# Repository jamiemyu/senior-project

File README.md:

# Senior_Design
Senior Design: Sleep State Analysis

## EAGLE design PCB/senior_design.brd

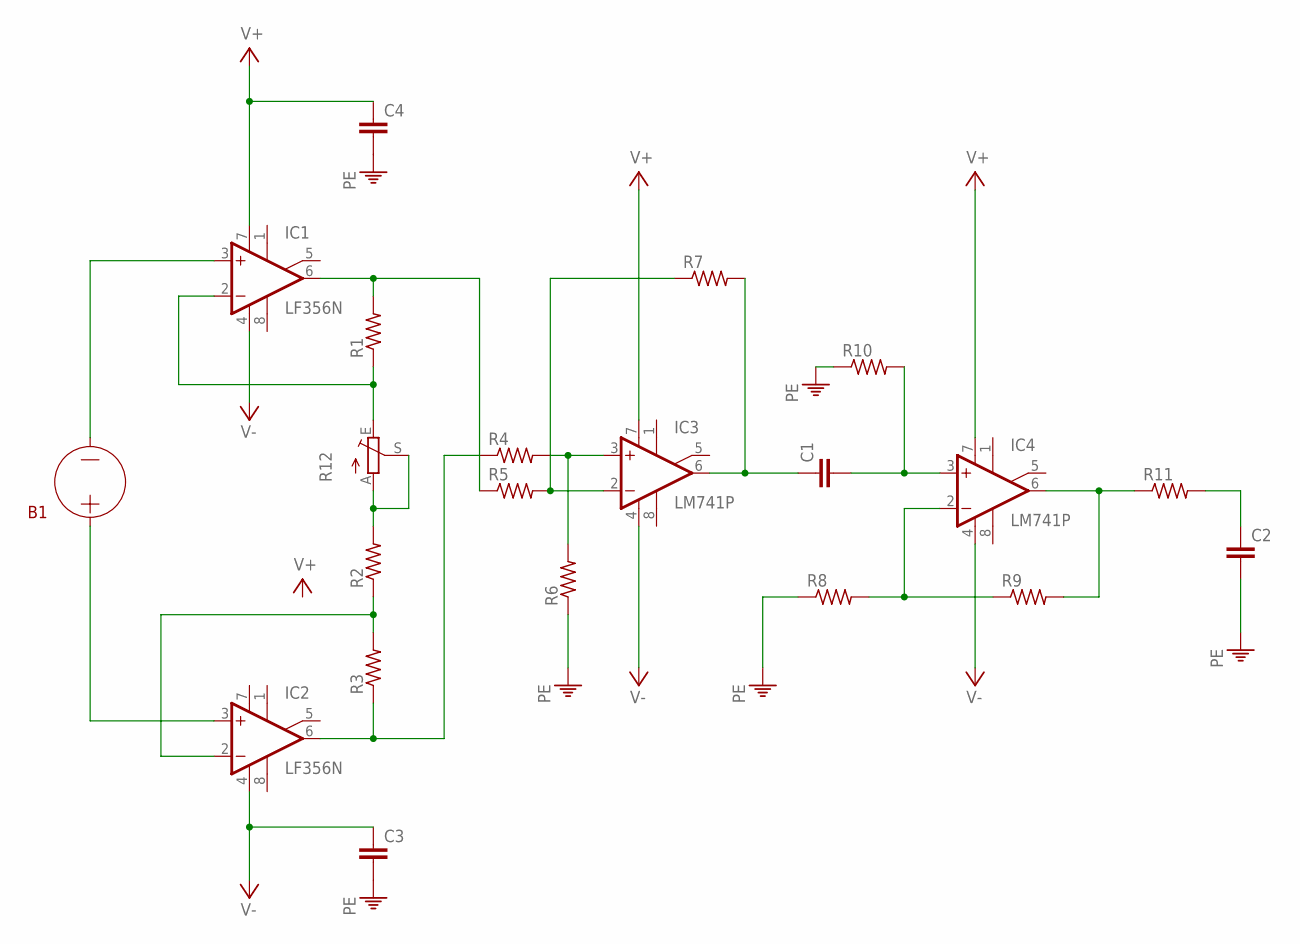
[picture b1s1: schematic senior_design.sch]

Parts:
C1, C2, C3, C4: C2,5-3; C2.5-3
IC1, IC2: LF356N; DIL08
IC3, IC4: LM741P; DIL08
R1, R2, R3, R4, R5, R6, R7, R8, R9, R10, R11: R-US_0204/7; 0204/7
R12: TRIM_EU-B25X; B25X

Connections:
unnamed: IC1.6 (OUT), R1.2, R5.1
unnamed: IC1.2 (-IN), R1.1, R12.E
unnamed: IC2.6 (OUT), R3.1, R4.1
unnamed: IC2.2 (-IN), R2.1, R3.2
unnamed: IC3.3 (+IN), R4.2, R6.2
unnamed: IC3.2 (-IN), R5.2, R7.1
unnamed: C2.1, R11.2
unnamed: C1.2, IC4.3 (+IN), R10.2
unnamed: C1.1, IC3.6 (OUT), R7.2
unnamed: IC4.2 (-IN), R8.2, R9.1
unnamed: IC4.6 (OUT), R9.2, R11.1
unnamed: R2.2, R12.A, R12.S
V+: C4.1, IC1.7 (V+), IC2.7 (V+), IC3.7 (V+), IC4.7 (V+)
V-: C3.1, IC1.4 (V-), IC2.4 (V-), IC3.4 (V-), IC4.4 (V-)
VO: C2.2, C3.2, C4.2, R6.1, R8.1, R10.1

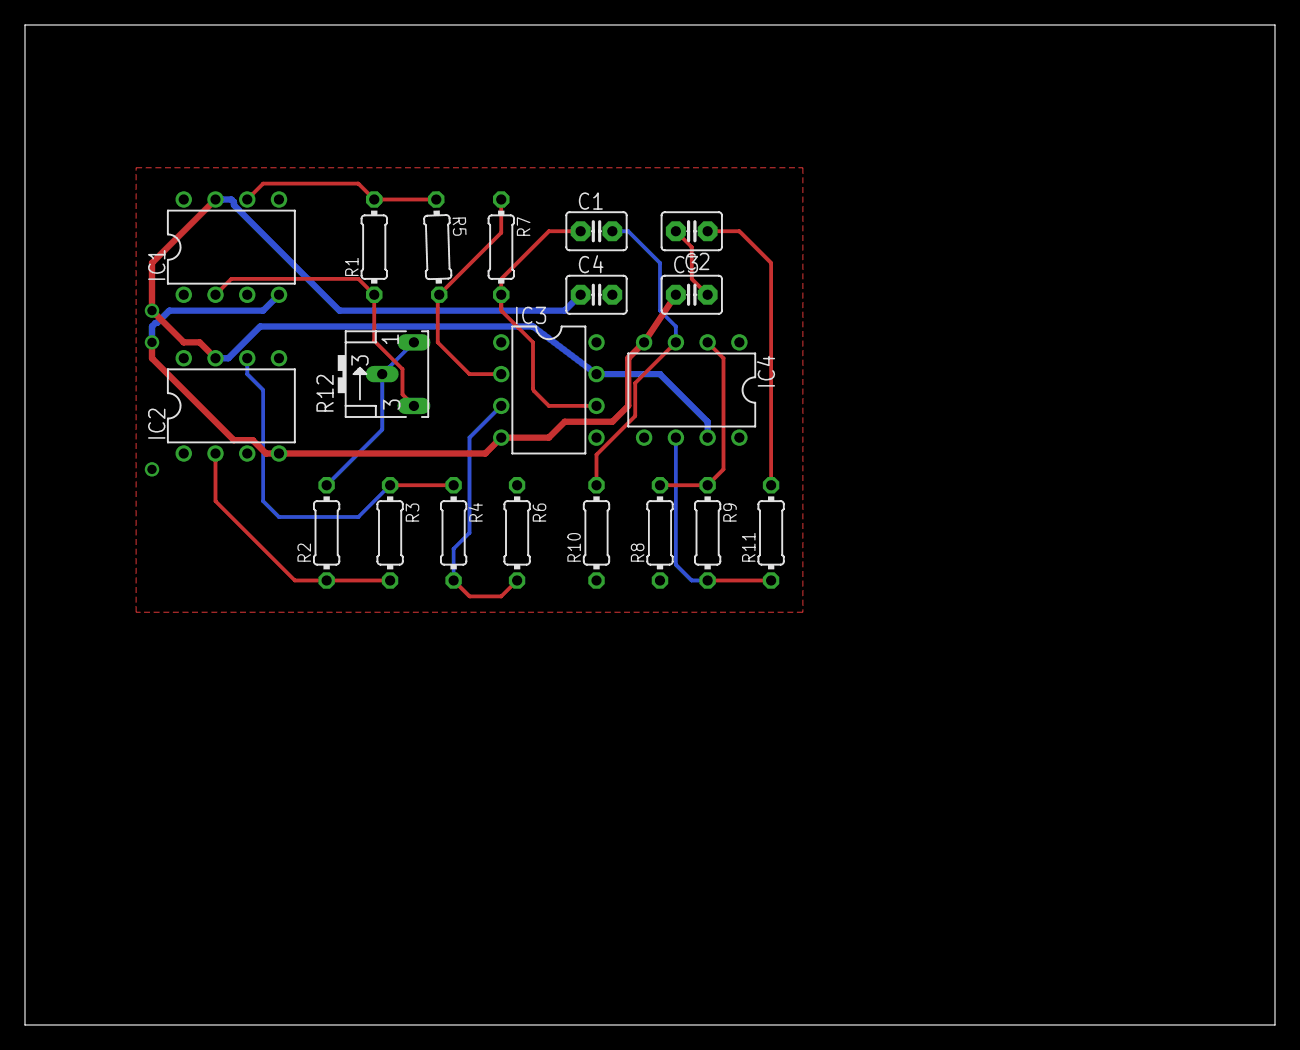
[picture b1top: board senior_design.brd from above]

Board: 2 copper layers, 100.0 x 80.0 mm, 20 parts (0 on the bottom side), 15 nets.

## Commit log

2017-09-29 initial sleep state analysis MATLAB code
2017-09-29 helper functions to process initial data files from physionet
2017-09-29 Refactored demo code by integrating helper functions and organizing plotting section
2017-10-09 latest algorithm development
2017-10-10 started building out the desktop application! Proof of concept that we can use Google Charts API within the app to render graphs.
2017-10-10 basic pie chart model for the sleep stages
2017-10-11 Attempts at building 4 separate bandpass filters for the four frequency bands (delta, theta, alpha, beta). Right now the filters are working, but in general there is still too much noise.
2017-10-13 Passband range corrected
2017-10-15 Change in filtering to implement 1 bandpass filter
2017-10-15 Update filtering to time domain processing of raw data
2017-10-15 Test average power at certain frequency ranges to determine differences between states
2017-10-15 Testing code. Uses stages 1 and 3 as examples to test the efficacy of my algorithm on scored sleep data
2017-10-16 Commit 10/15
2017-10-16 proof of concept using NodeJS to run MATLAB executable
2017-10-18 proof of concept connecting backend to frontendgit add .
2017-10-18 added input tag and submit button (+ spinner) to start analysis process design
2017-10-30 updates to HTML/CSS/JS. The MatlabClient can now process an opt_input for when the MATLAB function needs a filepath to load.
2017-10-30 Helper class used to parse data. TODO(Jamie): Add other parser functions for when MATLAB code is expanded to output more than just 3 values
2017-10-30 unit test for DataParser.
2017-10-30 rm node_modules from repo
2017-10-30 sleep icon
2017-11-01 Arduino Sketch
2017-11-01 Updates to folder/file names
2017-11-06 Testing code
2017-11-08 New code
2017-11-08 updates to codebase
2017-11-08 touching up UI
2017-11-12 Removed interrupt and added switch
2017-11-13 schematic
2017-11-14 updated classifier with wake, rem, light, and deep sleep
2017-11-14 Fixed Merge Errors
2017-11-14 updated algorithm to display using getDisplayInfo. Minor changes to JS in order to render 4-column chart
2017-11-14 fixed comment on final function call
2017-11-14 update subtitle
2017-11-14 current demo video
2017-11-24 uC debug sketches
2017-11-30 Final code
    Based on testing conducted in lap on the uno
2017-11-30 Updated schematics and pcb
2017-11-30 schematic clean up
2017-12-02 Helper functions and Testing Code
2017-12-02 More testing code
2017-12-04 Testing
2017-12-05 Testing code and algorithm updates
2017-12-05 Floor numSamples in getWindows function
2017-12-07 updated JS code to handle invalid file formats
2017-12-07 Testing code and power ratio improvements
2017-12-07 temporary branch to prevent files
2017-12-07 Final Test code for Technical Checkout
2017-12-07 rm node_modules
2017-12-08 Change fontsize of plot
2018-03-29 major refactoring of code for second iteration on UI
2018-07-25 adding all senior project code to new repo
